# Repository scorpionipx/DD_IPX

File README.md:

# DD_IPX

Auto tracking solar panel

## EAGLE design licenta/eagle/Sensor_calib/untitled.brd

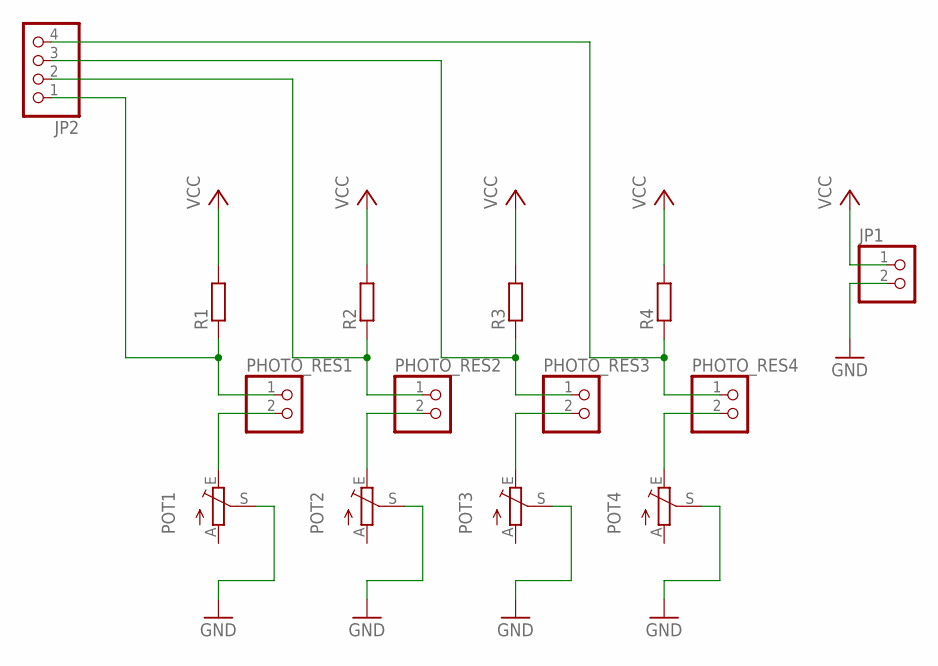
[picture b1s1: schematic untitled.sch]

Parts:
JP1: PINHD-1X2; 1X02
JP2: PINHD-1X4; 1X04
PHOTO_RES1, PHOTO_RES2, PHOTO_RES3, PHOTO_RES4: PINHD-1X2; 1X02
POT1, POT2, POT3, POT4: TRIM_EU-RJ9W; RJ9W
R1, R2, R3, R4: R-EU_0207/7; 0207/7

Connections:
GND: JP1.2, POT1.S, POT2.S, POT3.S, POT4.S
unnamed: JP2.1, PHOTO_RES1.1, R1.1
unnamed: PHOTO_RES1.2, POT1.E
unnamed: JP2.2, PHOTO_RES2.1, R2.1
unnamed: PHOTO_RES2.2, POT2.E
unnamed: JP2.3, PHOTO_RES3.1, R3.1
unnamed: PHOTO_RES3.2, POT3.E
unnamed: JP2.4, PHOTO_RES4.1, R4.1
unnamed: PHOTO_RES4.2, POT4.E
VCC: JP1.1, R1.2, R2.2, R3.2, R4.2

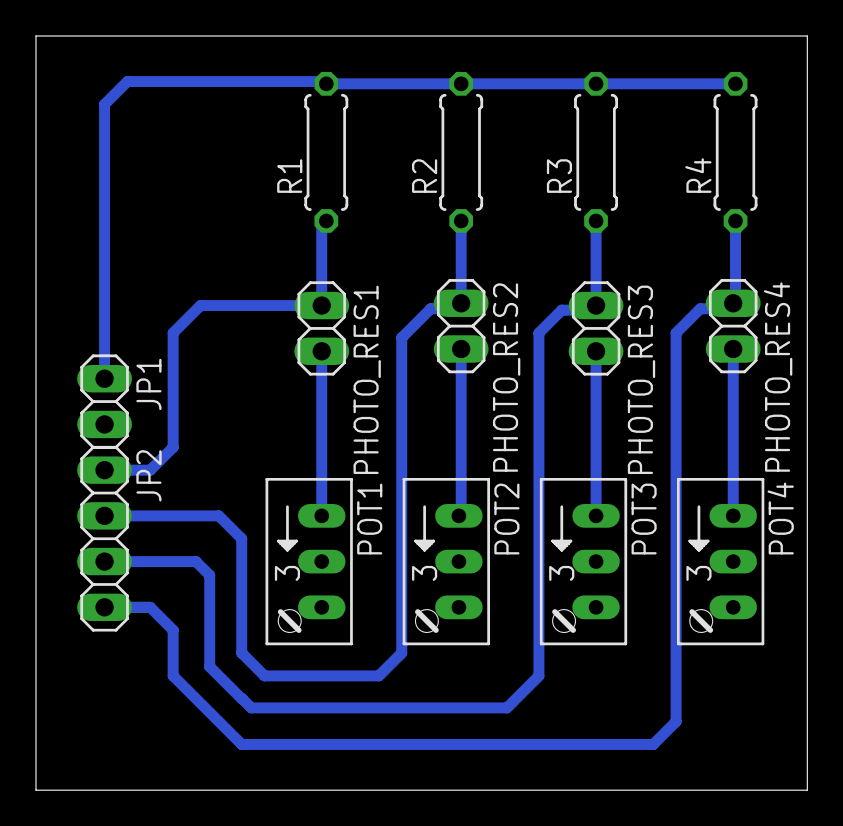
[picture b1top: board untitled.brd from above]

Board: 2 copper layers, 42.9 x 41.9 mm, 14 parts (0 on the bottom side), 10 nets.

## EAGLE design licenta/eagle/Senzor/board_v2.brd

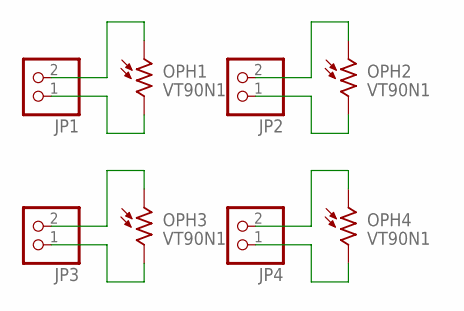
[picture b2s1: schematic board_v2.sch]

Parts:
JP1, JP2, JP3, JP4: PINHD-1X2; 1X02
OPH1, OPH2, OPH3, OPH4: VT90N1; VT900

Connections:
unnamed: JP1.2, OPH1.1
unnamed: JP1.1, OPH1.2
unnamed: JP2.2, OPH2.1
unnamed: JP2.1, OPH2.2
unnamed: JP3.2, OPH3.1
unnamed: JP3.1, OPH3.2
unnamed: JP4.2, OPH4.1
unnamed: JP4.1, OPH4.2

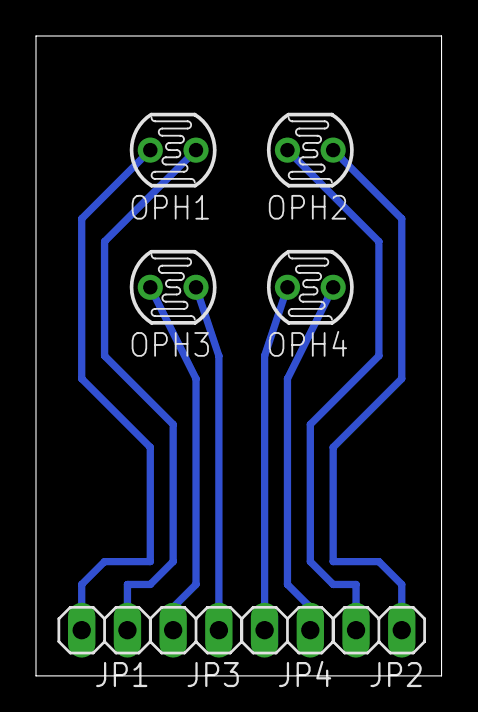
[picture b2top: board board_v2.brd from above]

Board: 2 copper layers, 22.5 x 35.5 mm, 8 parts (0 on the bottom side), 8 nets.

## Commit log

2018-03-18 Added main file
2018-03-18 Uploaded docs
2018-03-19 cuprins update
2018-03-19 Added code
2018-03-19 Bad code
2018-03-19 Good code
2018-03-19 Changed HX1230 control pins
    Added STATES;
    Configured IDLE STATE display setup
2018-03-19 Implemented joystick
2018-03-19 Manual control working
2018-03-20 Created project for 32a version
2018-03-20 First succesfull build - modified 32A specific registers
2018-03-20 Change PWM frecuency
2018-03-22 Fixed pwm frequency
2018-03-24 Battery nad converter voltage monitoring works
2018-03-25 Added my schematics
2018-03-25 eagle - sensor diana
2018-03-25 poze schema bloc
2018-03-25 document nou Diana
2018-03-31 update gitignore
2018-03-31 extreme burner, driver lcd
2018-03-31 modules
2018-04-18 intermediate version
2018-04-24 Motor control works fine
2018-04-25 pinout
2018-04-25 senzor layout
2018-04-25 eagle update
2018-05-03 concurs
2018-06-23 PD6 pin as relay controller
2018-06-23 PD5 as relay controller
2018-06-23 PD2 as relay driver
2018-06-23 New controller sch
2018-06-23 PB4 as relay driver
2018-06-23 updated sch
2018-06-23 Imagini utile
2018-06-23 ADDED SOME IMGS
2018-06-23 imagini
2018-06-23 images and updates
2018-06-23 more images and updates
2018-06-23 imagini cod
2018-06-23 buton
2018-06-23 go to bed
2018-06-24 GUI done
2018-06-24 convertor
2018-06-24 baterii
2018-06-24 releu
2018-06-25 4 chapters done
2018-06-25 It is fucking complete
2018-06-25 updated first page and title
2018-06-27 no message
2018-06-28 remove mistakes
2018-06-28 done
2018-06-28 anexe
2018-07-03 prezentare
